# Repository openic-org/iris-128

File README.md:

# Iris-128
Data and design files for Iris headstages

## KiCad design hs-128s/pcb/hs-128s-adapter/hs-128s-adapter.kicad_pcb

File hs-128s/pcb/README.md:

# HS-128s PCB

Stuff about the PCB.

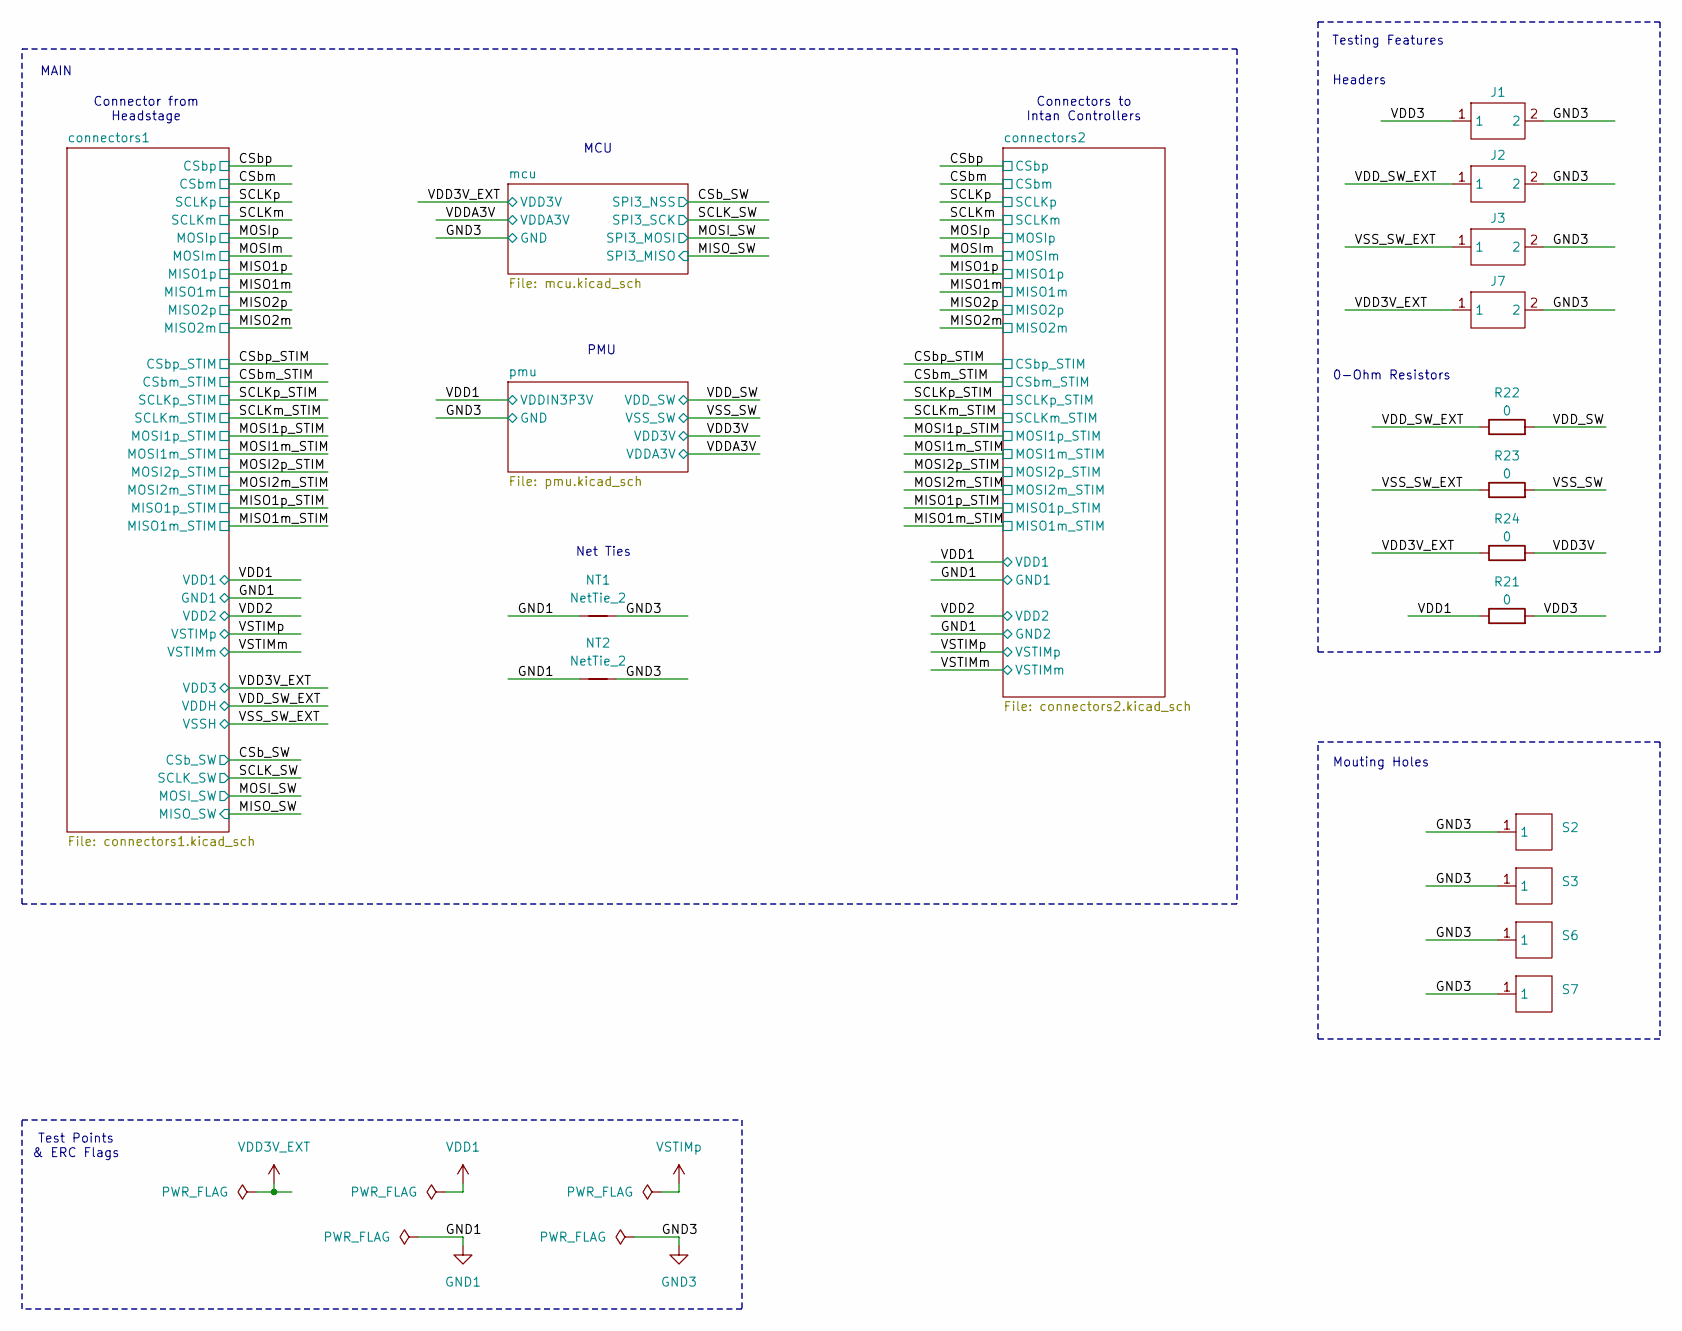
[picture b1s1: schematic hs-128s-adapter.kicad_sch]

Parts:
J1, J2, J3, J7: TLW-102-06-G-S; MPN TLW-102-06-G-S
NT1, NT2: NetTie_2; NetTie-2_SMD_Pad0.5mm; MPN None
R21, R22, R23, R24: 0; R_0402_1005Metric; MPN RC0402JR-070RL
S2, S3, S6, S7: MOUNTING_HOLE-PAD-0.1IN; MPN None

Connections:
/VDD3: J1.1, R21.2
/VDD3V: R24.2; also elsewhere on the board
/VDD_SW: R22.2; also elsewhere on the board
/VDD_SW_EXT: J2.1, R22.1; also elsewhere on the board
/VSS_SW: R23.2; also elsewhere on the board
/VSS_SW_EXT: J3.1, R23.1; also elsewhere on the board
GND1: NT1.1, NT2.1; also elsewhere on the board
GND3: J1.2, J2.2, J3.2, J7.2, NT1.2, NT2.2, S2.1, S3.1, S6.1, S7.1; also elsewhere on the board
VDD1: R21.1; also elsewhere on the board
VDD3V_EXT: J7.1, R24.1; also elsewhere on the board

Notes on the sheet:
Net Ties
MAIN
Connector from Headstage
Test Points & ERC Flags
Mouting Holes
Headers
MCU
PMU
0-Ohm Resistors
Connectors to Intan Controllers
Testing Features

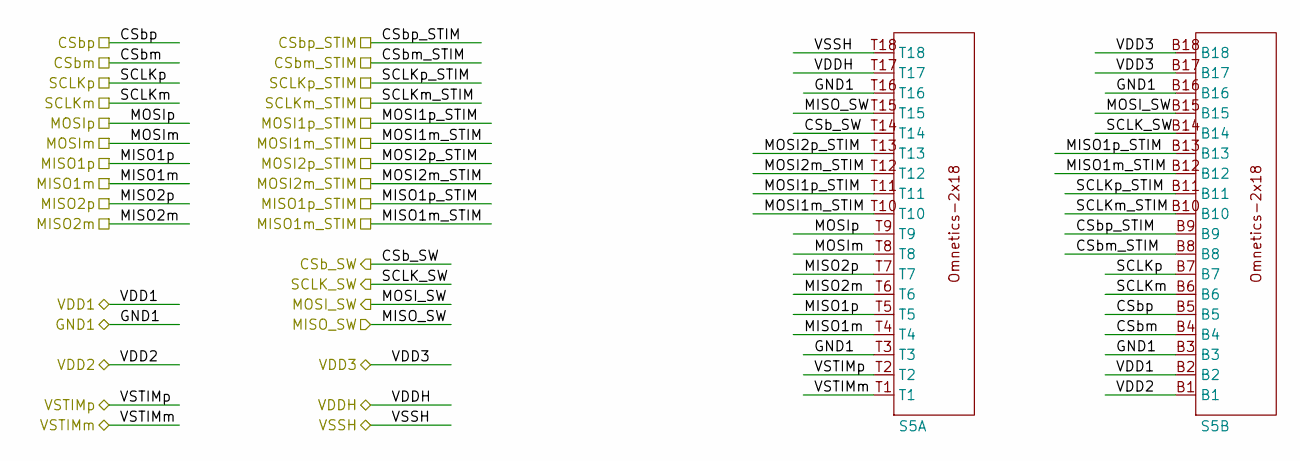
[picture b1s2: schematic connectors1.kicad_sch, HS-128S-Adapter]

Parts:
S5: OMNETICS-A79024-001; MPN A79024-001

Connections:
/CSb_SW: S5.T14; also elsewhere on the board
/CSbm: S5.B4; also elsewhere on the board
/CSbm_STIM: S5.B8; also elsewhere on the board
/CSbp: S5.B5; also elsewhere on the board
/CSbp_STIM: S5.B9; also elsewhere on the board
/MISO1m: S5.T4; also elsewhere on the board
/MISO1m_STIM: S5.B12; also elsewhere on the board
/MISO1p: S5.T5; also elsewhere on the board
/MISO1p_STIM: S5.B13; also elsewhere on the board
/MISO2m: S5.T6; also elsewhere on the board
/MISO2p: S5.T7; also elsewhere on the board
/MISO_SW: S5.T15; also elsewhere on the board
/MOSI1m_STIM: S5.T10; also elsewhere on the board
/MOSI1p_STIM: S5.T11; also elsewhere on the board
/MOSI2m_STIM: S5.T12; also elsewhere on the board
/MOSI2p_STIM: S5.T13; also elsewhere on the board
/MOSI_SW: S5.B15; also elsewhere on the board
/MOSIm: S5.T8; also elsewhere on the board
/MOSIp: S5.T9; also elsewhere on the board
/SCLK_SW: S5.B14; also elsewhere on the board
/SCLKm: S5.B6; also elsewhere on the board
/SCLKm_STIM: S5.B10; also elsewhere on the board
/SCLKp: S5.B7; also elsewhere on the board
/SCLKp_STIM: S5.B11; also elsewhere on the board
/VDD2: S5.B1; also elsewhere on the board
/VDD_SW_EXT: S5.T17; also elsewhere on the board
/VSS_SW_EXT: S5.T18; also elsewhere on the board
/VSTIMm: S5.T1; also elsewhere on the board
GND1: S5.B3, S5.B16, S5.T3, S5.T16; also elsewhere on the board
VDD1: S5.B2; also elsewhere on the board
VDD3V_EXT: S5.B17, S5.B18; also elsewhere on the board
VSTIMp: S5.T2; also elsewhere on the board

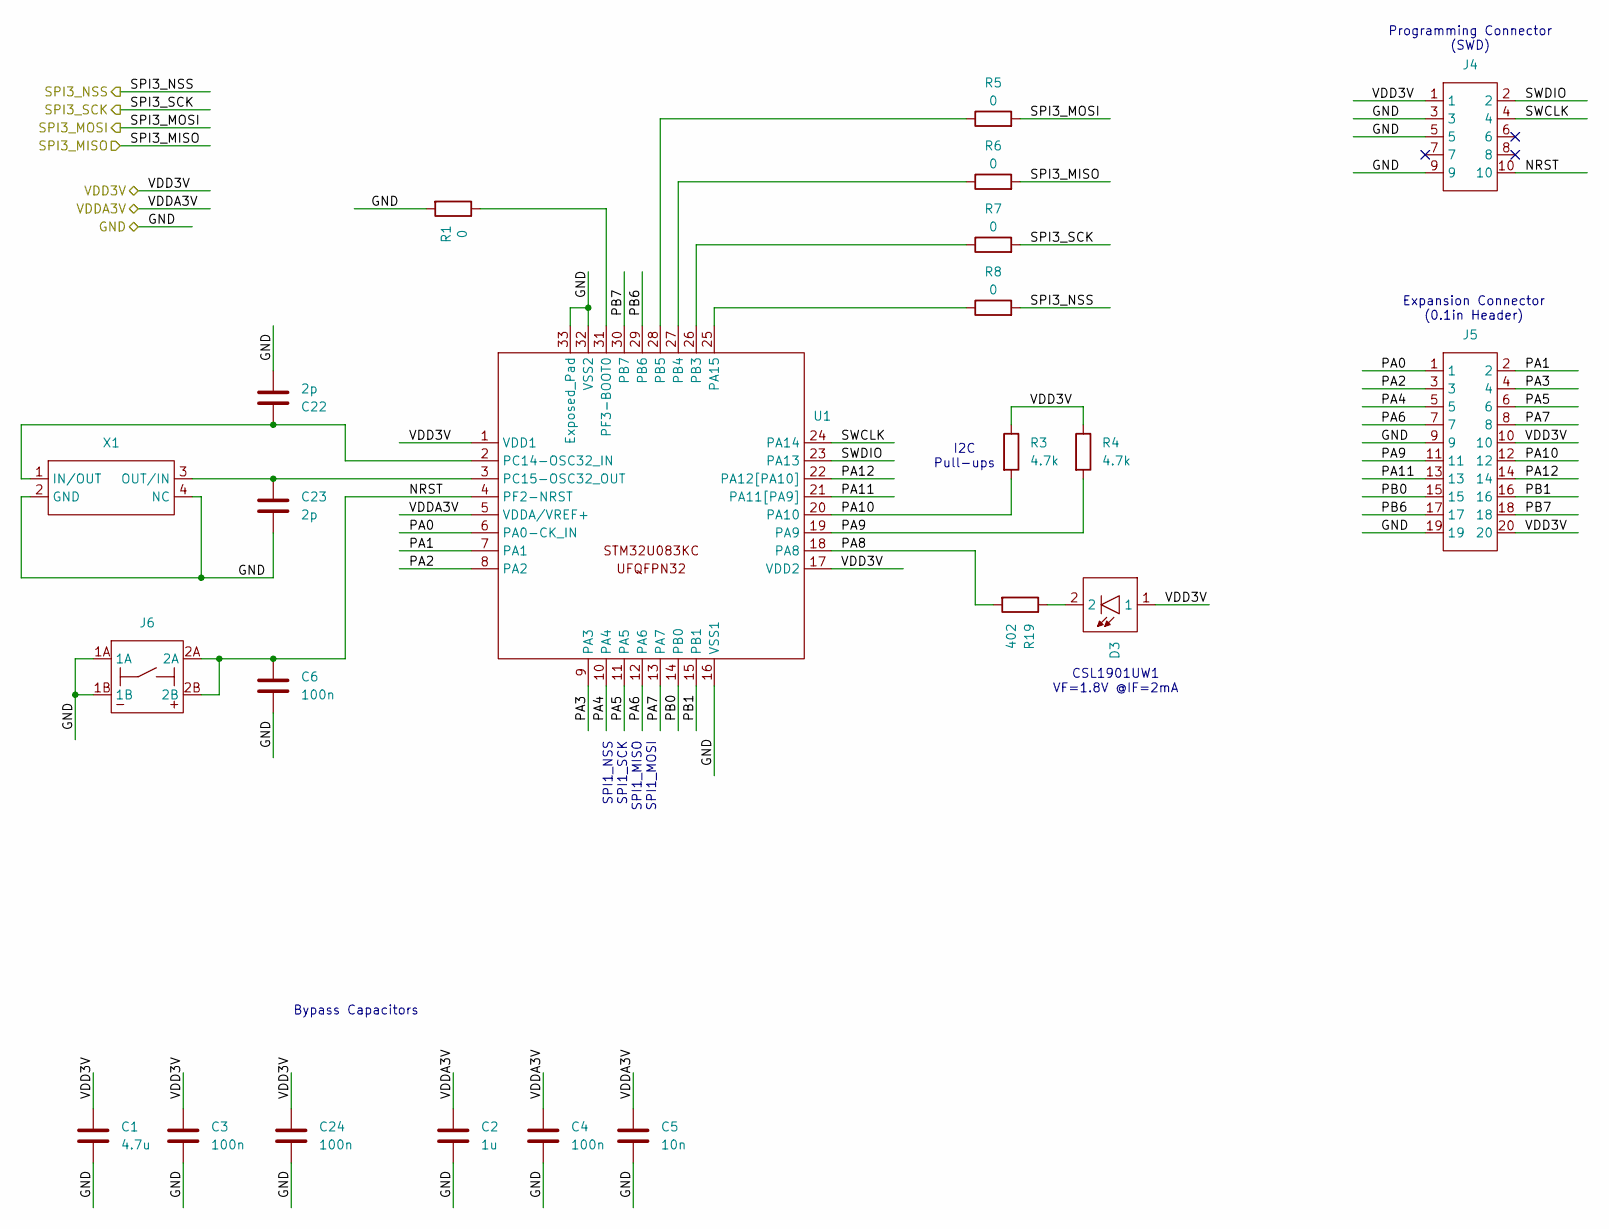
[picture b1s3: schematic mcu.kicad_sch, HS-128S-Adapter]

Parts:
C1: 4.7u; C_0402_1005Metric; MPN KGM05CR51C475MH
C2: 1u; C_0201_0603Metric; MPN GRM033R61C105ME15D
C3, C4, C6, C24: 100n; C_0201_0603Metric; MPN C0603X5R1C104K030BC
C5: 10n; C_0201_0603Metric; MPN GRM033R61C103KA12D
C22, C23: 2p; C_0201_0603Metric; MPN GJM0335C1E2R0WB01D
D3: ROHM-LED-0603; MPN CSL1901UW1
J4: SMD-ARM10-10_2x5_P0.05in; MPN FTSH-105-01-L-DV-K
J5: SLW-110-01-G-D; MPN SLW-110-01-G-D
J6: BOURNES-PUSHBUTTON-7914G-1-000; MPN 7914G-1-000
R1: 0; R_0201_0603Metric; MPN RC0201FR-070RL
R3, R4: 4.7k; R_0201_0603Metric; MPN RC0201FR-074K7L
R5, R6, R7, R8: 0; R_0402_1005Metric; MPN RC0402JR-070RL
R19: 402; R_0402_1005Metric; MPN RCS0402402RFKED
U1: UFQFPN-32-1EP_5x5mm_P0.5mm_EP3.6x3.6mm; MPN STM32U083KCU6
X1: CRYSTAL-ECS-ECX-1210B-32KHZ; MPN ECS-.327-6-1210B-N-TR

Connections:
/CSb_SW: R8.2; also elsewhere on the board
/MISO_SW: R6.2; also elsewhere on the board
/MOSI_SW: R5.2; also elsewhere on the board
/SCLK_SW: R7.2; also elsewhere on the board
/VDDA3V: C2.1, C4.1, C5.1, U1.5 (VDDA/VREF+); also elsewhere on the board
/mcu/NRST: C6.1, J4.10, J6.2A, J6.2B, U1.4 (PF2-NRST)
/mcu/PA0: J5.1, U1.6 (PA0-CK_IN)
/mcu/PA1: J5.2, U1.7 (PA1)
/mcu/PA2: J5.3, U1.8 (PA2)
/mcu/PA3: J5.4, U1.9 (PA3)
/mcu/PA4: J5.5, U1.10 (PA4)
/mcu/PA5: J5.6, U1.11 (PA5)
/mcu/PA6: J5.7, U1.12 (PA6)
/mcu/PA7: J5.8, U1.13 (PA7)
/mcu/PA8: R19.2, U1.18 (PA8)
/mcu/PA9: J5.11, R4.2, U1.19 (PA9)
/mcu/PA10: J5.12, R3.2, U1.20 (PA10)
/mcu/PA11: J5.13, U1.21 (PA11[PA9])
/mcu/PA12: J5.14, U1.22 (PA12[PA10])
/mcu/PB0: J5.15, U1.14 (PB0)
/mcu/PB1: J5.16, U1.15 (PB1)
/mcu/PB6: J5.17, U1.29 (PB6)
/mcu/PB7: J5.18, U1.30 (PB7)
/mcu/SWCLK: J4.4, U1.24 (PA14)
/mcu/SWDIO: J4.2, U1.23 (PA13)
GND3: C1.2, C2.2, C3.2, C4.2, C5.2, C6.2, C22.2, C23.2, C24.2, J4.3, J4.5, J4.9, J5.9, J5.19, J6.1A, J6.1B, R1.2, U1.16 (VSS1), U1.32 (VSS2), U1.33 (Exposed_Pad), X1.2 (GND), X1.4 (NC); also elsewhere on the board
unnamed: D3.2, R19.1
unnamed: R8.1, U1.25 (PA15)
unnamed: R7.1, U1.26 (PB3)
unnamed: R6.1, U1.27 (PB4)
unnamed: R5.1, U1.28 (PB5)
unnamed: C22.1, U1.2 (PC14-OSC32_IN), X1.1 (IN/OUT)
unnamed: C23.1, U1.3 (PC15-OSC32_OUT), X1.3 (OUT/IN)
unnamed: R1.1, U1.31 (PF3-BOOT0)
VDD3V_EXT: C1.1, C3.1, C24.1, D3.1, J4.1, J5.10, J5.20, R3.1, R4.1, U1.1 (VDD1), U1.17 (VDD2); also elsewhere on the board

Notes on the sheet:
I2C Pull-ups
SPI1_NSS SPI1_SCK SPI1_MISO SPI1_MOSI
CSL1901UW1 VF=1.8V @IF=2mA
Expansion Connector (0.1in Header)
Programming Connector (SWD)
Bypass Capacitors

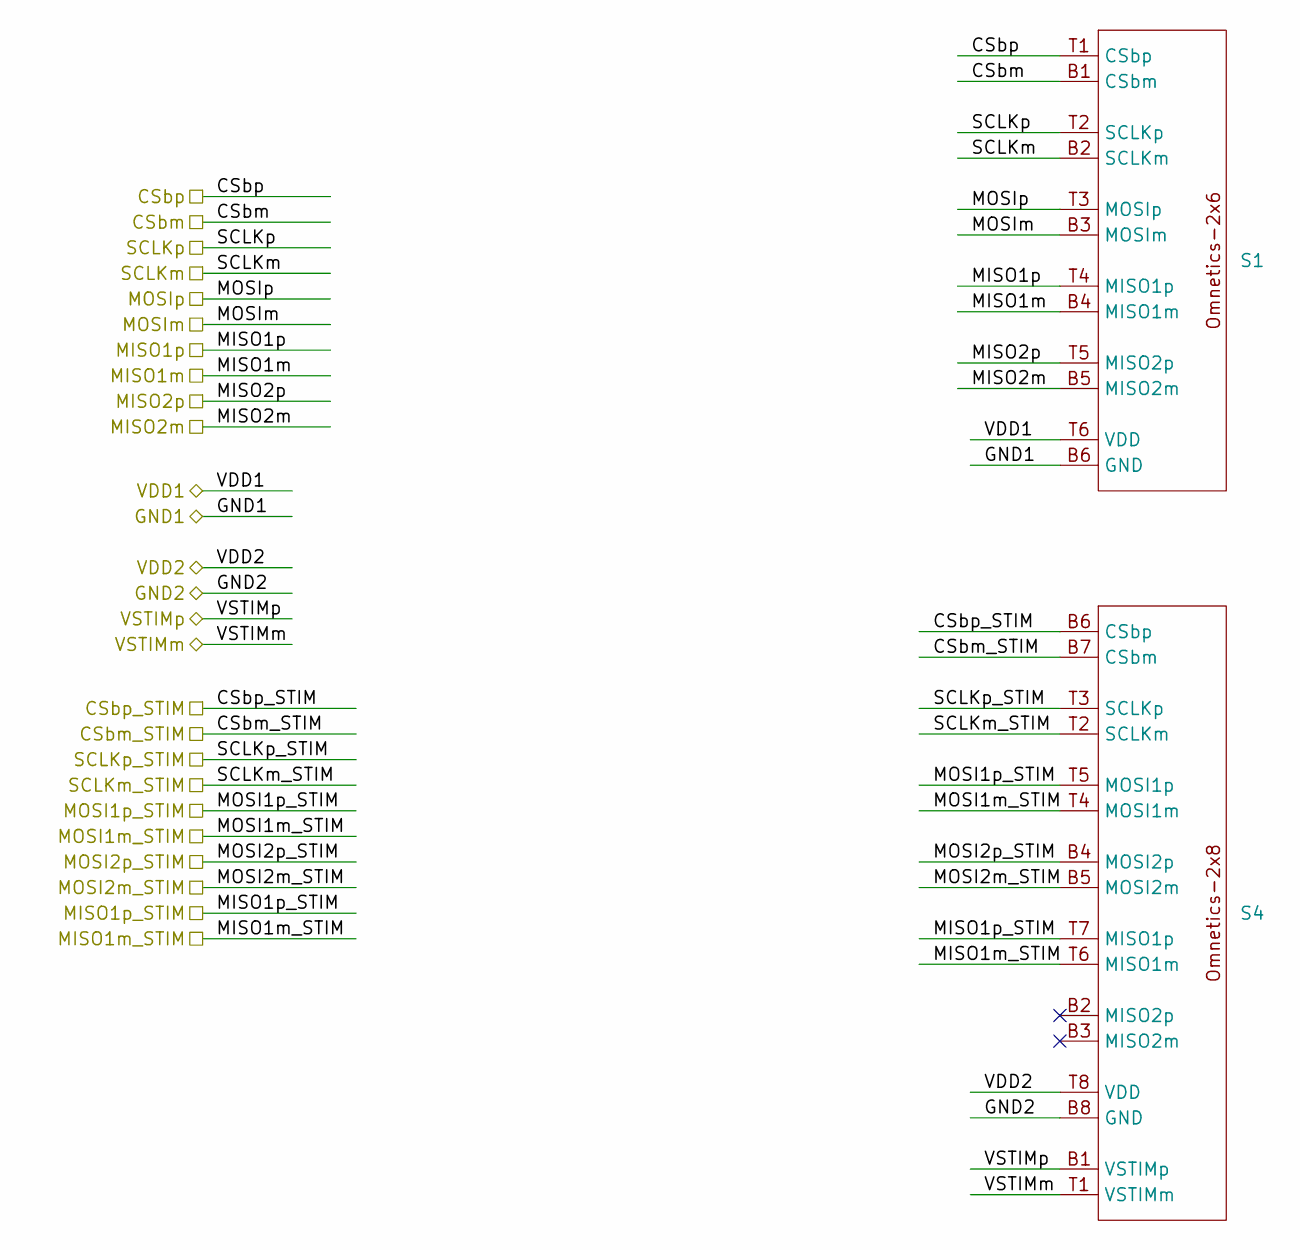
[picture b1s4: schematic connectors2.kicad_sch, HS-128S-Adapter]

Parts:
S1: OMNETICS_PZN-12-AA; MPN A79623-001
S4: OMNETICS_PZN-16-AA; MPN A79633-001

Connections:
/CSbm: S1.B1 (CSbm); also elsewhere on the board
/CSbm_STIM: S4.B7 (CSbm); also elsewhere on the board
/CSbp: S1.T1 (CSbp); also elsewhere on the board
/CSbp_STIM: S4.B6 (CSbp); also elsewhere on the board
/MISO1m: S1.B4 (MISO1m); also elsewhere on the board
/MISO1m_STIM: S4.T6 (MISO1m); also elsewhere on the board
/MISO1p: S1.T4 (MISO1p); also elsewhere on the board
/MISO1p_STIM: S4.T7 (MISO1p); also elsewhere on the board
/MISO2m: S1.B5 (MISO2m); also elsewhere on the board
/MISO2p: S1.T5 (MISO2p); also elsewhere on the board
/MOSI1m_STIM: S4.T4 (MOSI1m); also elsewhere on the board
/MOSI1p_STIM: S4.T5 (MOSI1p); also elsewhere on the board
/MOSI2m_STIM: S4.B5 (MOSI2m); also elsewhere on the board
/MOSI2p_STIM: S4.B4 (MOSI2p); also elsewhere on the board
/MOSIm: S1.B3 (MOSIm); also elsewhere on the board
/MOSIp: S1.T3 (MOSIp); also elsewhere on the board
/SCLKm: S1.B2 (SCLKm); also elsewhere on the board
/SCLKm_STIM: S4.T2 (SCLKm); also elsewhere on the board
/SCLKp: S1.T2 (SCLKp); also elsewhere on the board
/SCLKp_STIM: S4.T3 (SCLKp); also elsewhere on the board
/VDD2: S4.T8 (VDD); also elsewhere on the board
/VSTIMm: S4.T1 (VSTIMm); also elsewhere on the board
GND1: S1.B6 (GND), S4.B8 (GND); also elsewhere on the board
VDD1: S1.T6 (VDD); also elsewhere on the board
VSTIMp: S4.B1 (VSTIMp); also elsewhere on the board

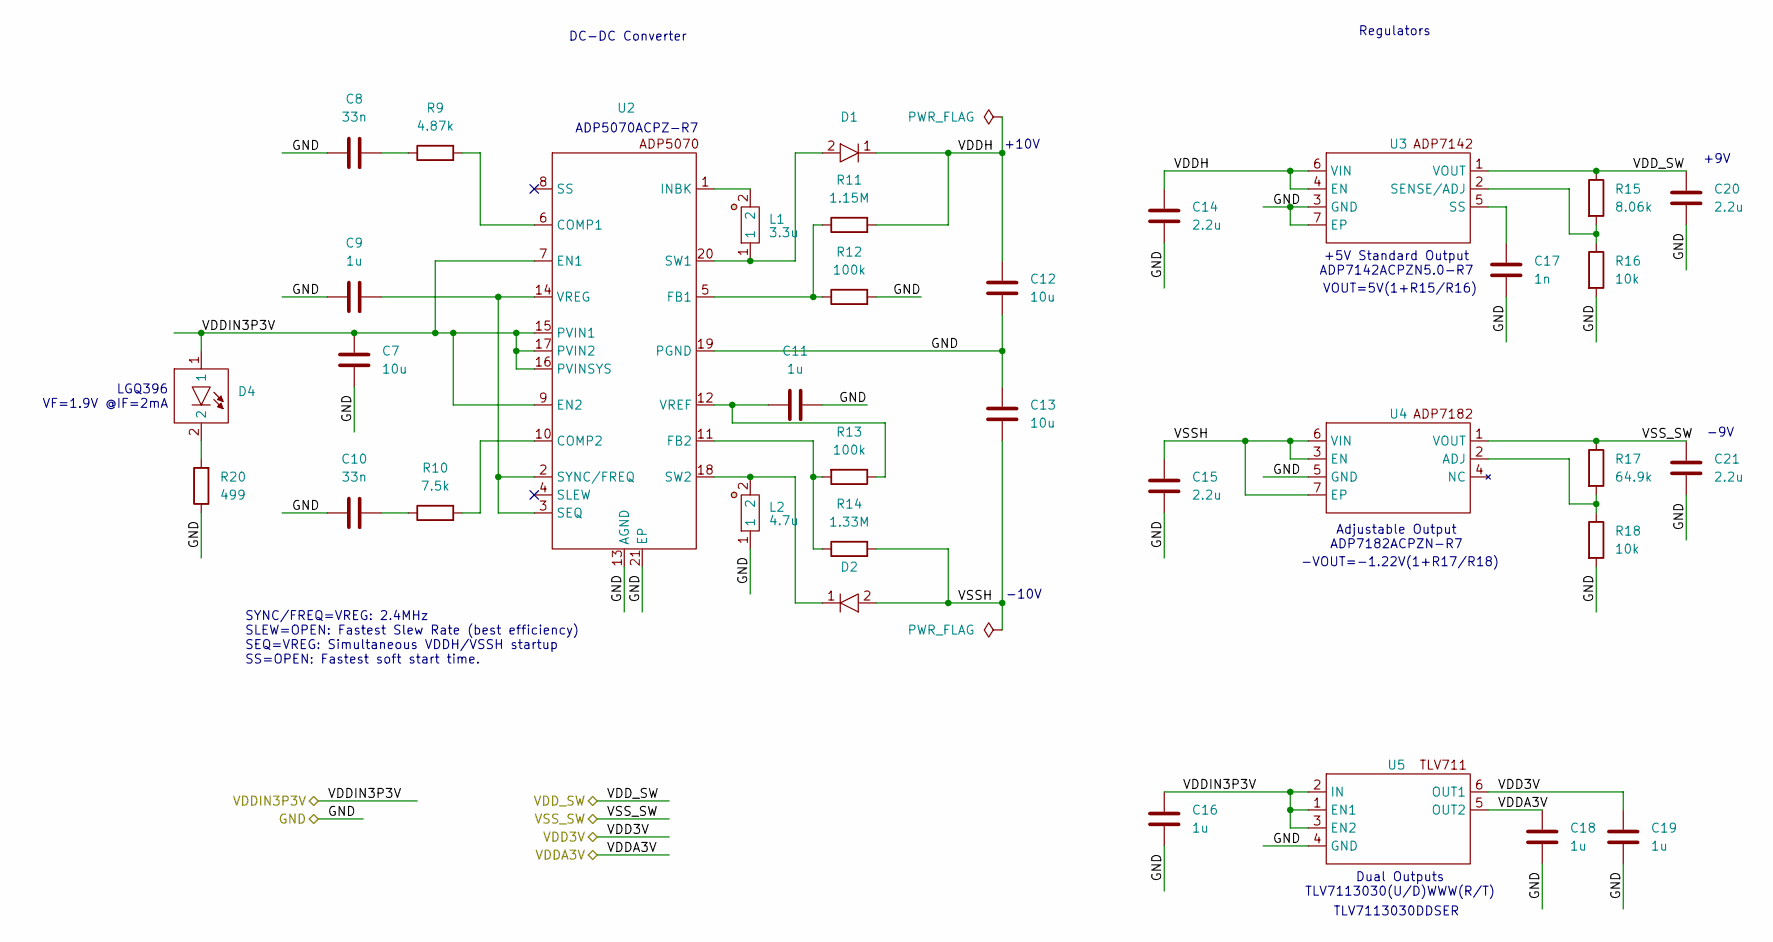
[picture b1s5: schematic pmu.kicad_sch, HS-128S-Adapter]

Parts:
C7, C12, C13: 10u; C_0603_1608Metric; MPN GRM188R61E106KA73D
C8, C10: 33n; C_0201_0603Metric; MPN GRM033R61C333KE84D
C9, C11, C16, C18, C19: 1u; C_0201_0603Metric; MPN GRM033R61C105ME15D
C14, C15, C20, C21: 2.2u; C_0201_0603Metric; MPN GRM035R61C225ME01D
C17: 1n; C_0201_0603Metric; MPN GRM033R61E102KA01J
D1, D2: X3-WLB1006-2; MPN SDM05U20CSP-7
D4: OSRAM-LED-0603; MPN LGQ396
L1: 3.3u; SMD-0808; MPN XFL2006-332MEC
L2: 4.7u; SMD-0808; MPN XFL2006-472MEC
R9: 4.87k; R_0201_0603Metric; MPN RC0201FR-074K87L
R10: 7.5k; R_0201_0603Metric; MPN RC0201FR-077K5L
R11: 1.15M; R_0201_0603Metric; MPN CRCW02011M15FNED
R12, R13: 100k; R_0201_0603Metric; MPN RC0201FR-07100KL
R14: 1.33M; R_0201_0603Metric; MPN CRCW02011M33FNED
R15: 8.06k; R_0201_0603Metric; MPN RC0201FR-078K06L
R16, R18: 10k; R_0201_0603Metric; MPN RC0201FR-0710KL
R17: 64.9k; R_0201_0603Metric; MPN RC0201FR-0764K9L
R20: 499; R_0402_1005Metric; MPN RCS0402499RFKED
U2: LFCSP-20-1EP_4mmx4mm_P0.5mm_EP2.6mm; MPN ADP5070ACPZ-R7
U3: LFCSP-6-1EP_2mmx2mm_P0.65mm_EP1.6mmx1mm; MPN ADP7142ACPZN5.0-R7
U4: LFCSP-6-1EP_2mmx2mm_P0.65mm_EP1.6mmx1mm; MPN ADP7182ACPZN-R7
U5: WSON-6_1.5mmx1.5mm_P0.5mm; MPN TLV7113030DDSER

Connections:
/VDD3V: C19.1, U5.6 (OUT1); also elsewhere on the board
/VDDA3V: C18.1, U5.5 (OUT2); also elsewhere on the board
/VDD_SW: C20.1, R15.1, U3.1 (VOUT); also elsewhere on the board
/VSS_SW: C21.1, R17.1, U4.1 (VOUT); also elsewhere on the board
/pmu/VDDH: C12.1, C14.1, D1.1, R11.2, U3.4 (EN), U3.6 (VIN)
/pmu/VSSH: C13.2, C15.1, D2.2, R14.2, U4.3 (EN), U4.6 (VIN), U4.7 (EP)
GND3: C7.2, C8.1, C9.1, C10.1, C11.2, C12.2, C13.1, C14.2, C15.2, C16.2, C17.2, C18.2, C19.2, C20.2, C21.2, L2.1, R12.2, R16.2, R18.2, R20.1, U2.13 (AGND), U2.19 (PGND), U2.21 (EP), U3.3 (GND), U3.7 (EP), U4.5 (GND), U5.4 (GND); also elsewhere on the board
unnamed: C8.2, R9.1
unnamed: C10.2, R10.1
unnamed: D4.2, R20.2
unnamed: R9.2, U2.6 (COMP1)
unnamed: R10.2, U2.10 (COMP2)
unnamed: R11.1, R12.1, U2.5 (FB1)
unnamed: R13.2, R14.1, U2.11 (FB2)
unnamed: L1.2, U2.1 (INBK)
unnamed: C9.2, U2.2 (SYNC/FREQ), U2.3 (SEQ), U2.14 (VREG)
unnamed: D1.2, L1.1, U2.20 (SW1)
unnamed: D2.1, L2.2, U2.18 (SW2)
unnamed: C11.1, R13.1, U2.12 (VREF)
unnamed: R15.2, R16.1, U3.2 (SENSE/ADJ)
unnamed: C17.1, U3.5 (SS)
unnamed: R17.2, R18.1, U4.2 (ADJ)
VDD1: C7.1, C16.1, D4.1, U2.7 (EN1), U2.9 (EN2), U2.15 (PVIN1), U2.16 (PVINSYS), U2.17 (PVIN2), U5.1 (EN1), U5.2 (IN), U5.3 (EN2); also elsewhere on the board

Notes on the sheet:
Regulators
LGQ396 VF=1.9V @IF=2mA
-9V
DC-DC Converter
-10V
Adjustable Output ADP7182ACPZN-R7
ADP5070ACPZ-R7
Dual Outputs TLV7113030(U/D)WWW(R/T)
+9V
+5V Standard Output ADP7142ACPZN5.0-R7
SYNC/FREQ=VREG: 2.4MHz SLEW=OPEN: Fastest Slew Rate (best efficiency) SEQ=VREG: Simultaneous VDDH/VSSH startup SS=OPEN: Fastest soft start time.
TLV7113030DDSER
+10V
VOUT=5V(1+R15/R16)
-VOUT=-1.22V(1+R17/R18)

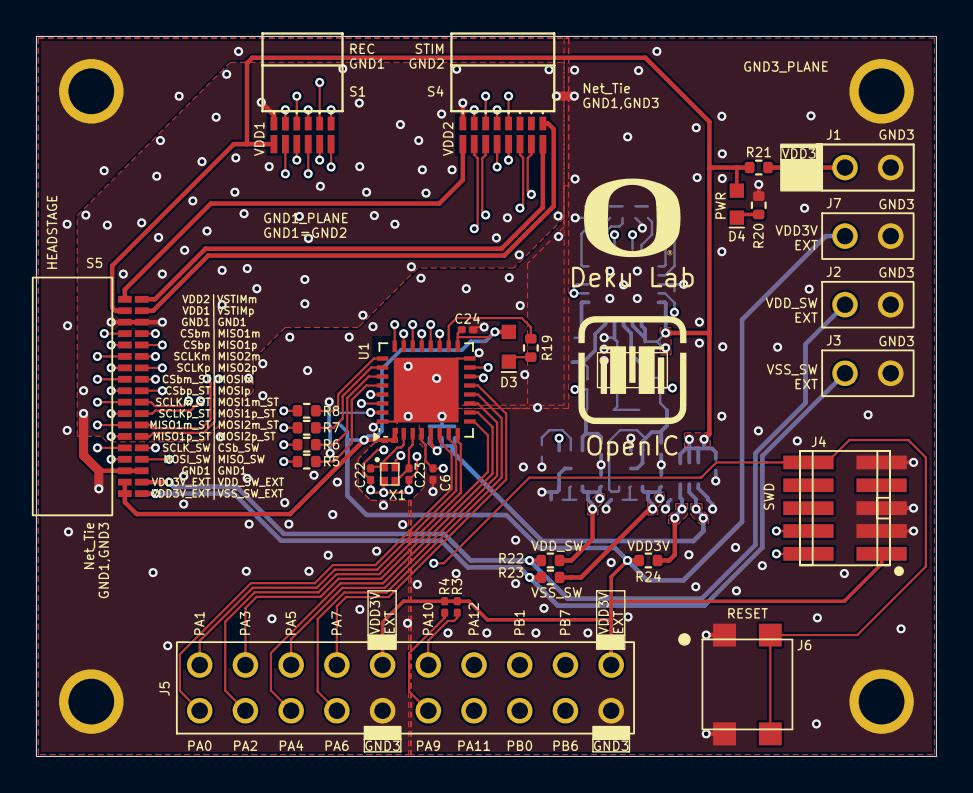
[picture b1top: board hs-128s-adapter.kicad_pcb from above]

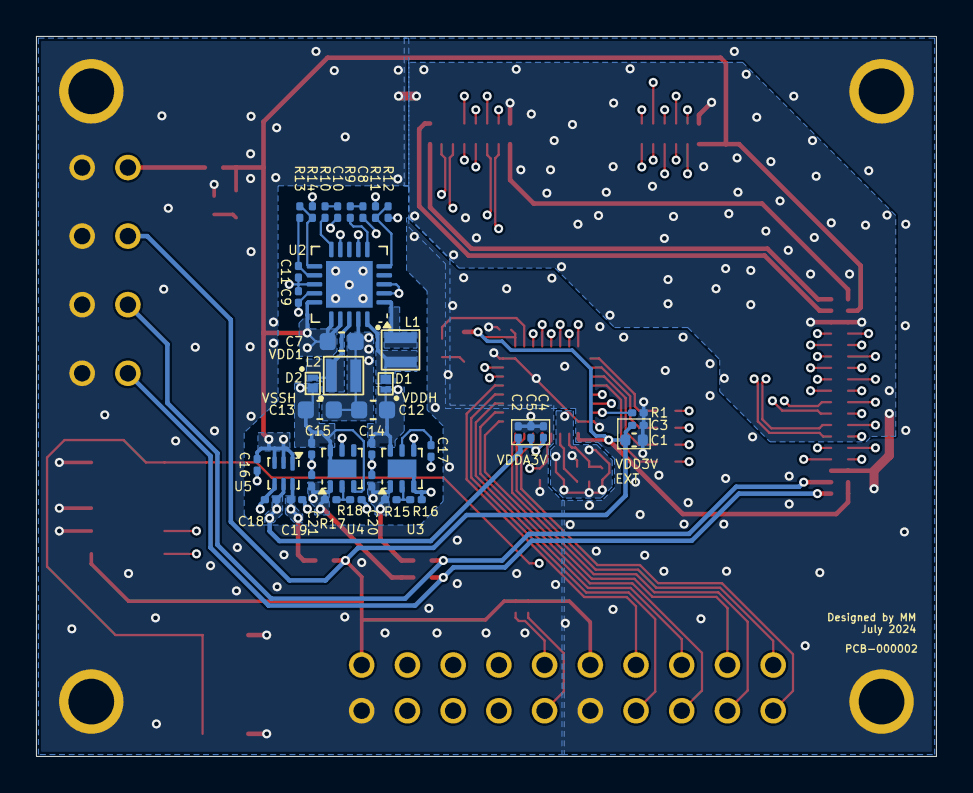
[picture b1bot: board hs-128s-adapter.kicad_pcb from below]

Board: 4 copper layers, 50.0 x 40.0 mm, 75 parts (39 on the bottom side), 83 nets.

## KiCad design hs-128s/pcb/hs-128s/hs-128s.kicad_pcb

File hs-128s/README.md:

# HS-128S Board

Stuff about this board.

<!-- a photo of the device, not the 3D model from KiCad -->

## Description

Description text.

## Specifications

* Spec 1.
* Spec 2.
* Feature 1.
* Feature 2.

## File Structure

Details about file structure.

## File Types

Table describing file types.

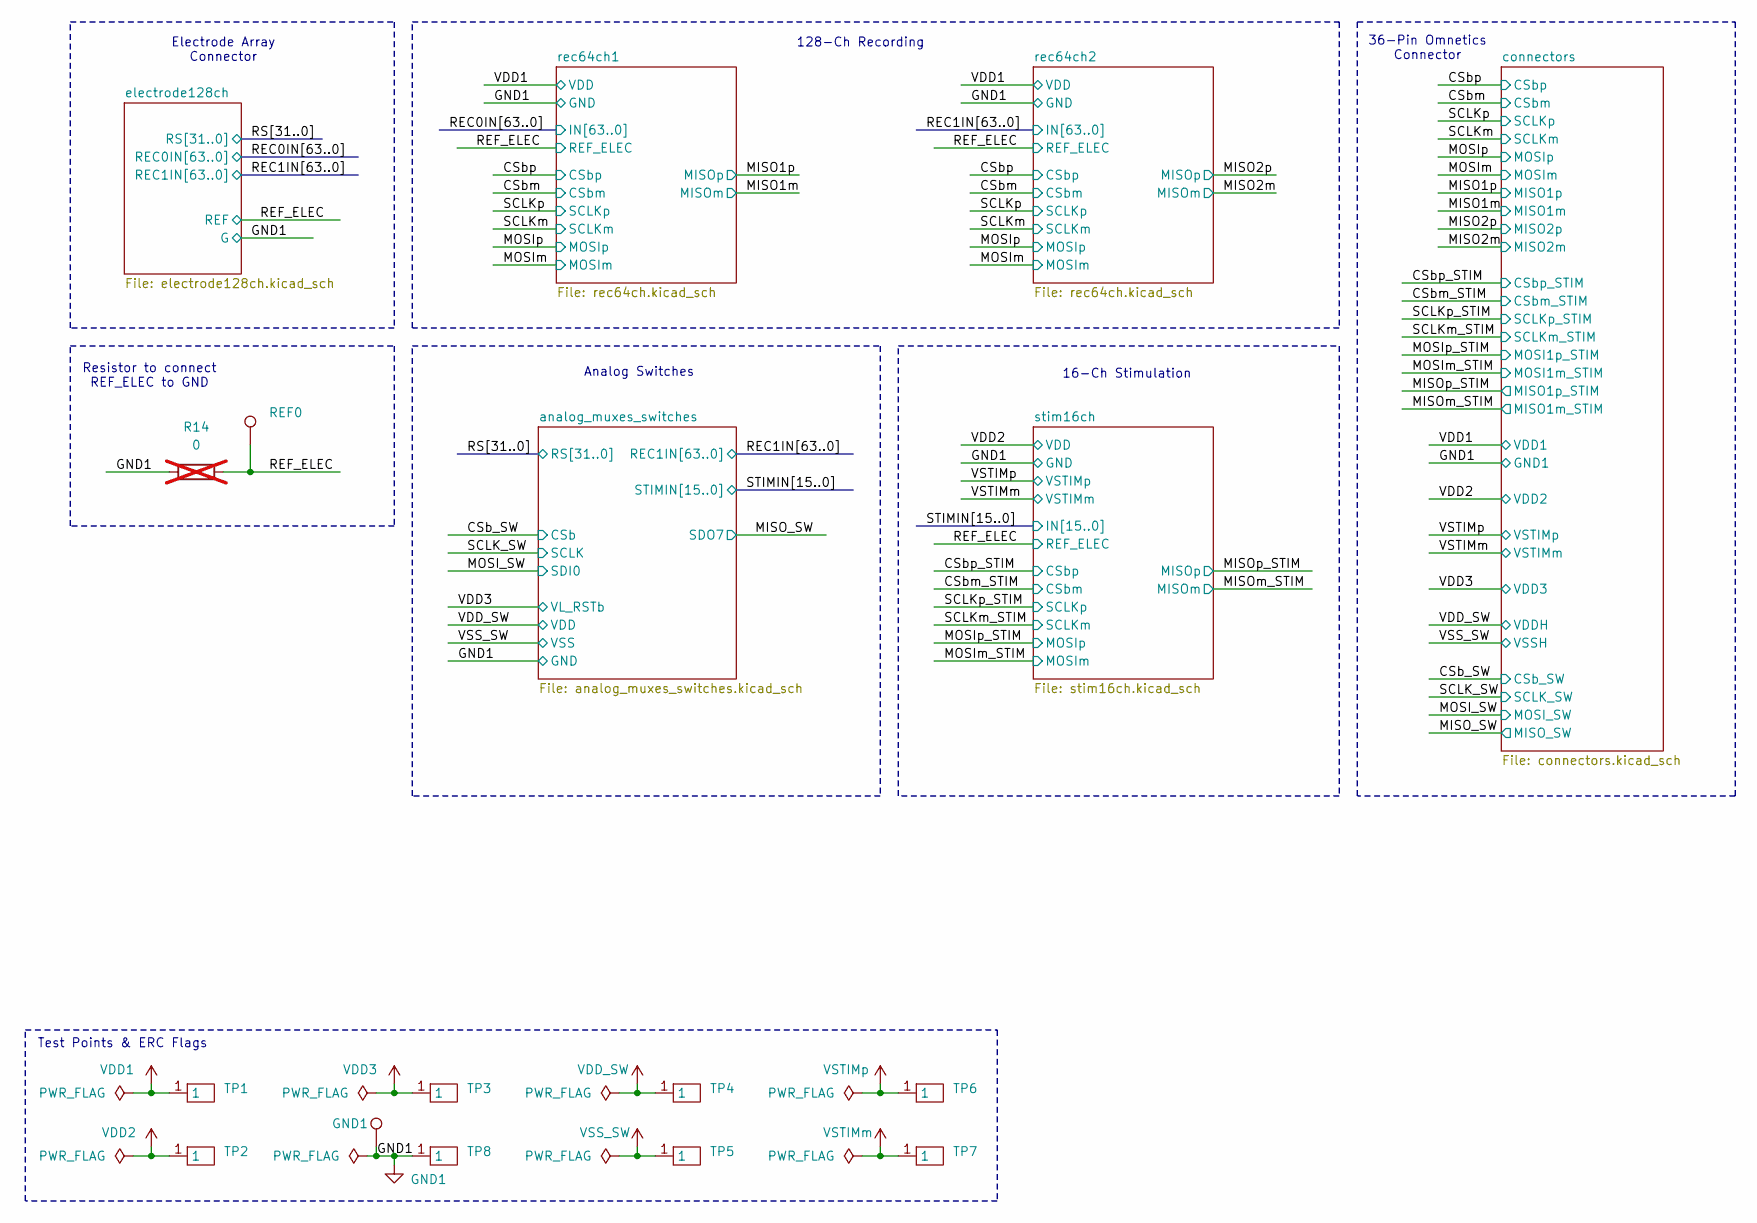
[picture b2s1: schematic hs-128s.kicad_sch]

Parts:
GND1: GND1; TESTPOINT_SMALL
R14: 0; R_0402_1005Metric; not fitted
REF0: REF0; TESTPOINT_SMALL
TP1, TP2, TP3, TP4, TP5, TP6, TP7, TP8: TESTPOINT_PAD_SQ_0.5

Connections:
/REF_ELEC: R14.2, REF0.1; also elsewhere on the board
GND1: GND1.1, R14.1, TP8.1; also elsewhere on the board
VDD1: TP1.1; also elsewhere on the board
VDD2: TP2.1; also elsewhere on the board
VDD3: TP3.1; also elsewhere on the board
VDD_SW: TP4.1; also elsewhere on the board
VSS_SW: TP5.1; also elsewhere on the board
VSTIMm: TP7.1; also elsewhere on the board
VSTIMp: TP6.1; also elsewhere on the board

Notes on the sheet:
Resistor to connect REF_ELEC to GND
Analog Switches
16-Ch Stimulation
128-Ch Recording
Electrode Array Connector
Test Points & ERC Flags
36-Pin Omnetics Connector
